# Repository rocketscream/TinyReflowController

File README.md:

# Tiny Reflow Controller

An all-in-one Arduino compatible reflow controller powered by ATmega328P (V2) or ATtiny1634R (V1). A reincarnation of the Reflow Oven Controller Shield that requires an external Arduino board like Arduino Uno based on user feedbacks over the years. Powered by the ATmega328P/ATtiny1634R coupled with the latest thermocouple sensor interface IC MAX31856 from Maxim, we managed to remove the need of an Arduino board and reduce the overall cost. We also use as much SMD parts in this revision to keep the cost low (manual soldering and left over residue cleaning is time consuming) and leaving only the terminal block and the LCD connector on through hole version. We also managed to streamline all components to run on 3.3V to further simplify the design. 

All you need is an external Solid State Relay (SSR) (rated accordingly to your oven), K type thermocouple (we recommend those with fiber glass or steel jacket), and an oven of course! 

You can now select to run a lead-free profile or leaded profile from the selection switch. 

V2 comes with 0.96" 128*64 OLED LCD to plot the real-time reflow curve and has a built-in serial-USB interface. V2 also has an optional transistor output drive fan if needed. 

## Building

Use VS Code with platform IO. Set the version you want to build in platform.ini

## Profile Configration

 - Each Profile has 4 stages: pre-heat, soak, reflow and cooldown
 - Each Stage has:
    - Max Temp: The Max Temperature for this stage in degree C. Goal Temp.
    - Micro Time: Milliseconds until the next temperature setpoint increase. (set to 0 for max heating speed)
    - Heat Step: Degree C step size for new setpoint (set to "Max Temp" - "previous stage max" (TEMPERATURE_ROOM for first stage) for max heating speed)
    - Hold Micro Time: Milliseconds to hold at max temp once it is reached (set to 0 to skip)
    - PID KP: 
    - PID KI: 
    - PID KD: 

## Profiles

Profiles can be configured in src/main.cpp starting on line 108.

### Leaded Reflow Curve (Kester EP256)
```
  Temperature (Degree Celcius)         Magic Happens Here!
  219-|                                       x  x
      |                                    x        x
      |                                 x              x
  180-|                              x                    x
      |                         x    |                    |   x
      |                    x         |                    |       x
  150-|               x              |                    |           x
      |             x |              |                    |
      |           x   |              |                    |
      |         x     |              |                    |
      |       x       |              |                    |
      |     x         |              |                    |
      |   x           |              |                    |
  30 -| x             |              |                    |
      |<  60 - 90 s  >|<  60 - 90 s >|<   60 - 90 s      >|
      | Preheat Stage | Soaking Stage|   Reflow Stage     | Cool
   0  |_ _ _ _ _ _ _ _|_ _ _ _ _ _ _ |_ _ _ _ _ _ _ _ _ _ |_ _ _ _ _ _ _ _ _ _ _
                                                                 Time (Seconds)
```

### Lead-Free Reflow Curve
```
  Temperature (Degree Celcius)                 Magic Happens Here!
  245-|                                               x  x
      |                                            x        x
      |                                         x              x
      |                                      x                    x
  200-|                                   x                          x
      |                              x    |                          |   x
      |                         x         |                          |       x
      |                    x              |                          |
  150-|               x                   |                          |
      |             x |                   |                          |
      |           x   |                   |                          |
      |         x     |                   |                          |
      |       x       |                   |                          |
      |     x         |                   |                          |
      |   x           |                   |                          |
  30 -| x             |                   |                          |
      |<  60 - 90 s  >|<    90 - 120 s   >|<       90 - 120 s       >|
      | Preheat Stage |   Soaking Stage   |       Reflow Stage       | Cool
   0  |_ _ _ _ _ _ _ _|_ _ _ _ _ _ _ _ _ _|_ _ _ _ _ _ _ _ _ _ _ _ _ |_ _ _ _ _
                                                                 Time (Seconds)
```

### PLA Annealing
```
  Temperature (Degree Celcius)
      |                                     
  63 -|               x   x   x   x   x   x    
      |             x |                   |   x
      |           x   |                   |       x  
      |         x     |                   |           x
      |       x       |                   |               x
      |     x         |                   |                   x
      |   x           |                   |                        x
  30 -| x             |                   |                          |
      |<   4 hours   >|<      30 min     >|<      3 hours           >|
      | Preheat Stage |   Soaking Stage   |          Cool            |
   0  |_ _ _ _ _ _ _ _|_ _ _ _ _ _ _ _ _ _|_ _ _ _ _ _ _ _ _ _ _ _ _ |_ _ _ _ _
                                                                 Time (Seconds)
```

### PETG Annealing
```
  Temperature (Degree Celcius)
      |                                     
  177-|               x   x   x   x   x   x    
      |             x |                   |   x
      |           x   |                   |       x  
      |         x     |                   |           x
      |       x       |                   |               x
      |     x         |                   |                   x
      |   x           |                   |                        x
  30 -| x             |                   |                          |
      |<   4 hours   >|<      30 min     >|<      3 hours           >|
      | Preheat Stage |   Soaking Stage   |          Cool            |
   0  |_ _ _ _ _ _ _ _|_ _ _ _ _ _ _ _ _ _|_ _ _ _ _ _ _ _ _ _ _ _ _ |_ _ _ _ _
                                                                 Time (Seconds)
```

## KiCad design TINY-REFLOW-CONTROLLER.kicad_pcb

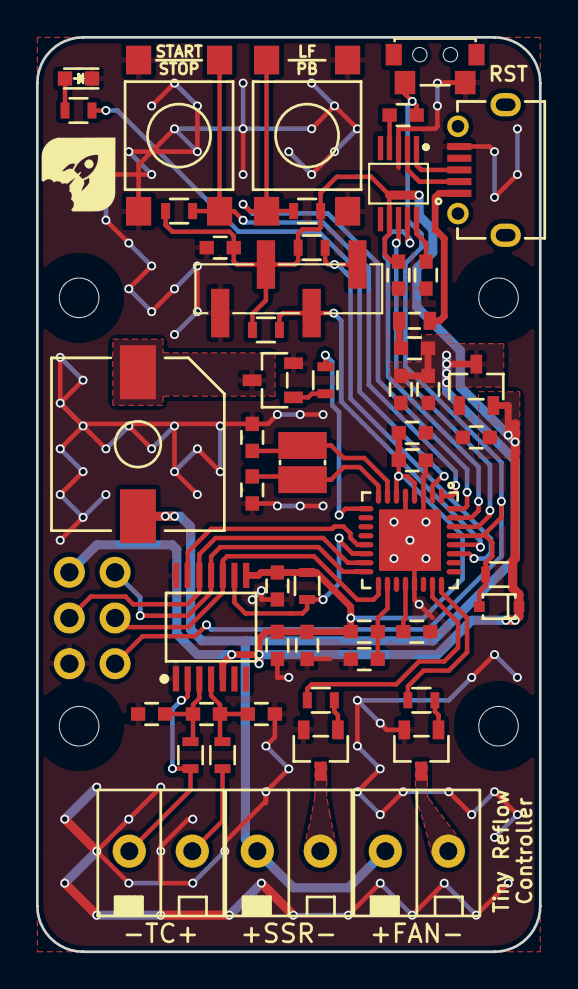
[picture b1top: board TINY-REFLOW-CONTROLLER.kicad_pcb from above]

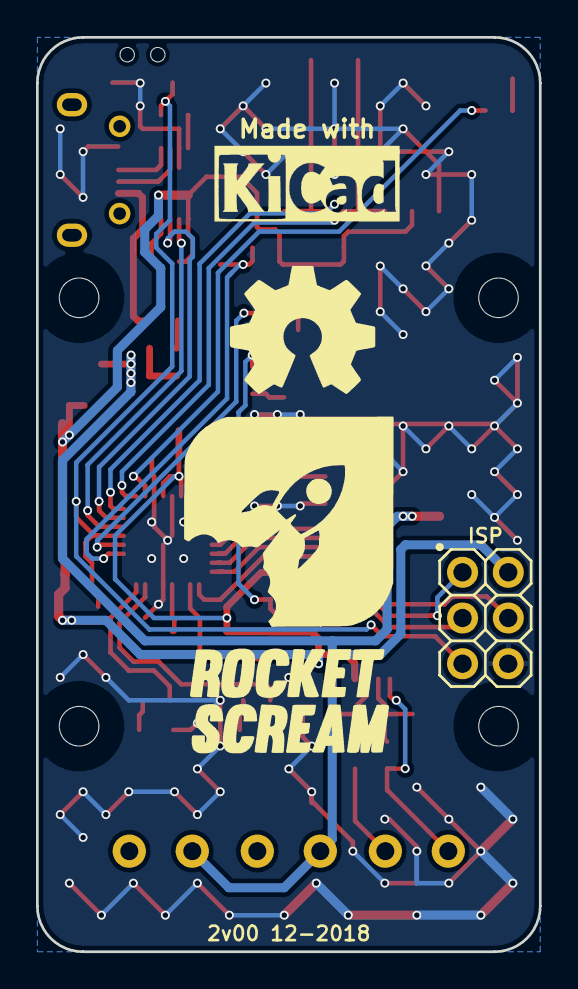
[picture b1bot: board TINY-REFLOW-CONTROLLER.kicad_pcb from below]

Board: 2 copper layers, 27.9 x 50.8 mm, 58 parts (4 on the bottom side), 40 nets.

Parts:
C1, C2: 10nF; C_0603
C3, C4, C6, C7, C8, C9, C11, C13, C14, C17, C18, C19: 100nF; C_0603
C5, C10, C12: 10uF 16V X5R; C_0603
C15, C16: 10pF; C_0603
D1: Red; LED_0603
D3: 1N4148WS; SOD-323
F1: FUSE; MF-FSMF
J1, J2, J5: TERMINAL-BLOCK-1x2; TB-1776275-2
J3: MICRO-USB
J4: 2.54mm 2x3; HDR_2x3_Pitch2.54mm
L1: BLM18KG221SN1D; I_0603
L2: LBMF1608T100K; I_0603
LOGO1: LOGO-ROCKET-SCREAM; LOGO-ROCKET-SCREAM_Without_Text_XXXSmall
LOGO2: LOGO-KICAD; LOGO-KICAD_XSmall
LOGO3: LOGO-ROCKET-SCREAM; LOGO-ROCKET-SCREAM_Vertical_Small
LOGO4: LOGO-OSHW; LOGO-OSHW_Small
LS1: HYG9605B
Q1, Q2, Q3: 2N3904; SOT-23
R1, R6, R11: 2K2; R_0603
R2, R3: 100R; R_0603
R4, R5, R9, R10: 10K; R_0603
R7: 27K; R_0603
R8, R12: 53K6; R_0603
SW1, SW2: IT-1109S; IT-1102W
SW3: TS-018
U1: ATMEGA328P-MU; QFN-32_5x5mm_Pitch0.5mm
U2: MCP1700T-3302E-TT; SOT-23
U3: MAX31856; TSSOP-14
U4: CH340E; MSOP-10
U5: OLED-SSD1306-128X64-I2C
Y1: NX3225GD

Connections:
3V3: C5.1, C6.1, C8.1, C9.1, C10.2, C11.1, C13.1, C19.1, D3.1, J4.2, L2.2, R1.1, R4.1, R5.1, R9.2, R10.1, R11.1, U1.4, U1.6, U2.2, U3.5, U3.8, U4.7, U5.2
5V0: C4.1, C12.1, J2.1, J5.1, L1.2, LS1.1, U2.3
/A0: R8.1, U1.23
/A1: R12.1, U1.24
/D0: U1.30, U4.8
/D1: U1.31, U4.9
/D2: R5.2, SW2.1, SW2.2, U1.32
/D3: R4.2, SW1.3, SW1.4, U1.1
/D4: R6.2, U1.2
/D5: R7.1, U1.9
/D9: U1.13, U3.13
/D10: R10.2, U1.14, U3.9
/D11: J4.4, U1.15, U3.12
/D12: J4.1, U1.16, U3.11
/D13: J4.3, U1.17, U3.10
/RST: C7.2, D3.2, J4.5, R9.1, SW3.1, U1.29
/SCL: R1.2, U1.28, U5.3
/SDA: R11.2, U1.27, U5.4
/TC+: J1.2, R3.1
/TC-: J1.1, R2.1, U3.2
AREF: C18.1, U1.20
GND: C1.2, C2.2, C4.2, C5.2, C6.2, C8.2, C9.2, C10.1, C11.2, C12.2, C13.2, C14.2, C15.2, C16.2, C17.2, C18.2, C19.2, D1.1, J3.5, J4.6, Q1.2, Q2.2, Q3.2, SW1.1, SW1.2, SW2.3, SW2.4, SW3.2, U1.3, U1.5, U1.21, U1.33, U2.1, U3.1, U3.14, U4.3, U5.1
unnamed: C1.1, C3.1, R2.2, U3.3
unnamed: C2.1, C3.2, R3.2, U3.4
unnamed: C7.1, U4.4
unnamed: C14.1, U4.10
unnamed: C15.1, U1.7, Y1.1
unnamed: C16.1, U1.8, Y1.2
unnamed: C17.1, L2.1, U1.18
unnamed: D1.2, R6.1
unnamed: F1.2, L1.1
unnamed: J2.2, Q2.3
unnamed: J3.2, U4.2
unnamed: J3.3, U4.1
unnamed: J5.2, Q3.3
unnamed: LS1.2, Q1.3
unnamed: Q1.1, R7.2
unnamed: Q2.1, R8.2
unnamed: Q3.1, R12.2
VUSB: F1.1, J3.1

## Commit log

2017-09-11 CC-BY-SA-4.0
2017-09-11 Version 1.0
2017-10-03 Rename TINY-REFLOW-CONTROLLER-0R20.sch to TINY-REFLOW-CONTROLLER.sch
2017-10-03 Rename TINY-REFLOW-CONTROLLER-0R20-cache.lib to TINY-REFLOW-CONTROLLER-cache.lib
2017-10-03 Rename TINY-REFLOW-CONTROLLER-0R20.kicad_pcb to TINY-REFLOW-CONTROLLER.kicad_pcb
2017-10-03 Rename TINY-REFLOW-CONTROLLER-0R20.pro to TINY-REFLOW-CONTROLLER.pro
2017-10-03 Rename TINY-REFLOW-CONTROLLER-0R0.pdf to TINY-REFLOW-CONTROLLER.pdf
2018-03-02 Added gerber files
2019-03-31 Version 2.0
2020-04-24 Added description of changes from official version
2020-04-28 Fixed fan animation
2020-04-30 Adjusted text alignment on graph
2020-10-24 Multiple Profiles and Temp Holding
2020-10-24 Cleanup
2021-10-21 Modified code for ESP8266
